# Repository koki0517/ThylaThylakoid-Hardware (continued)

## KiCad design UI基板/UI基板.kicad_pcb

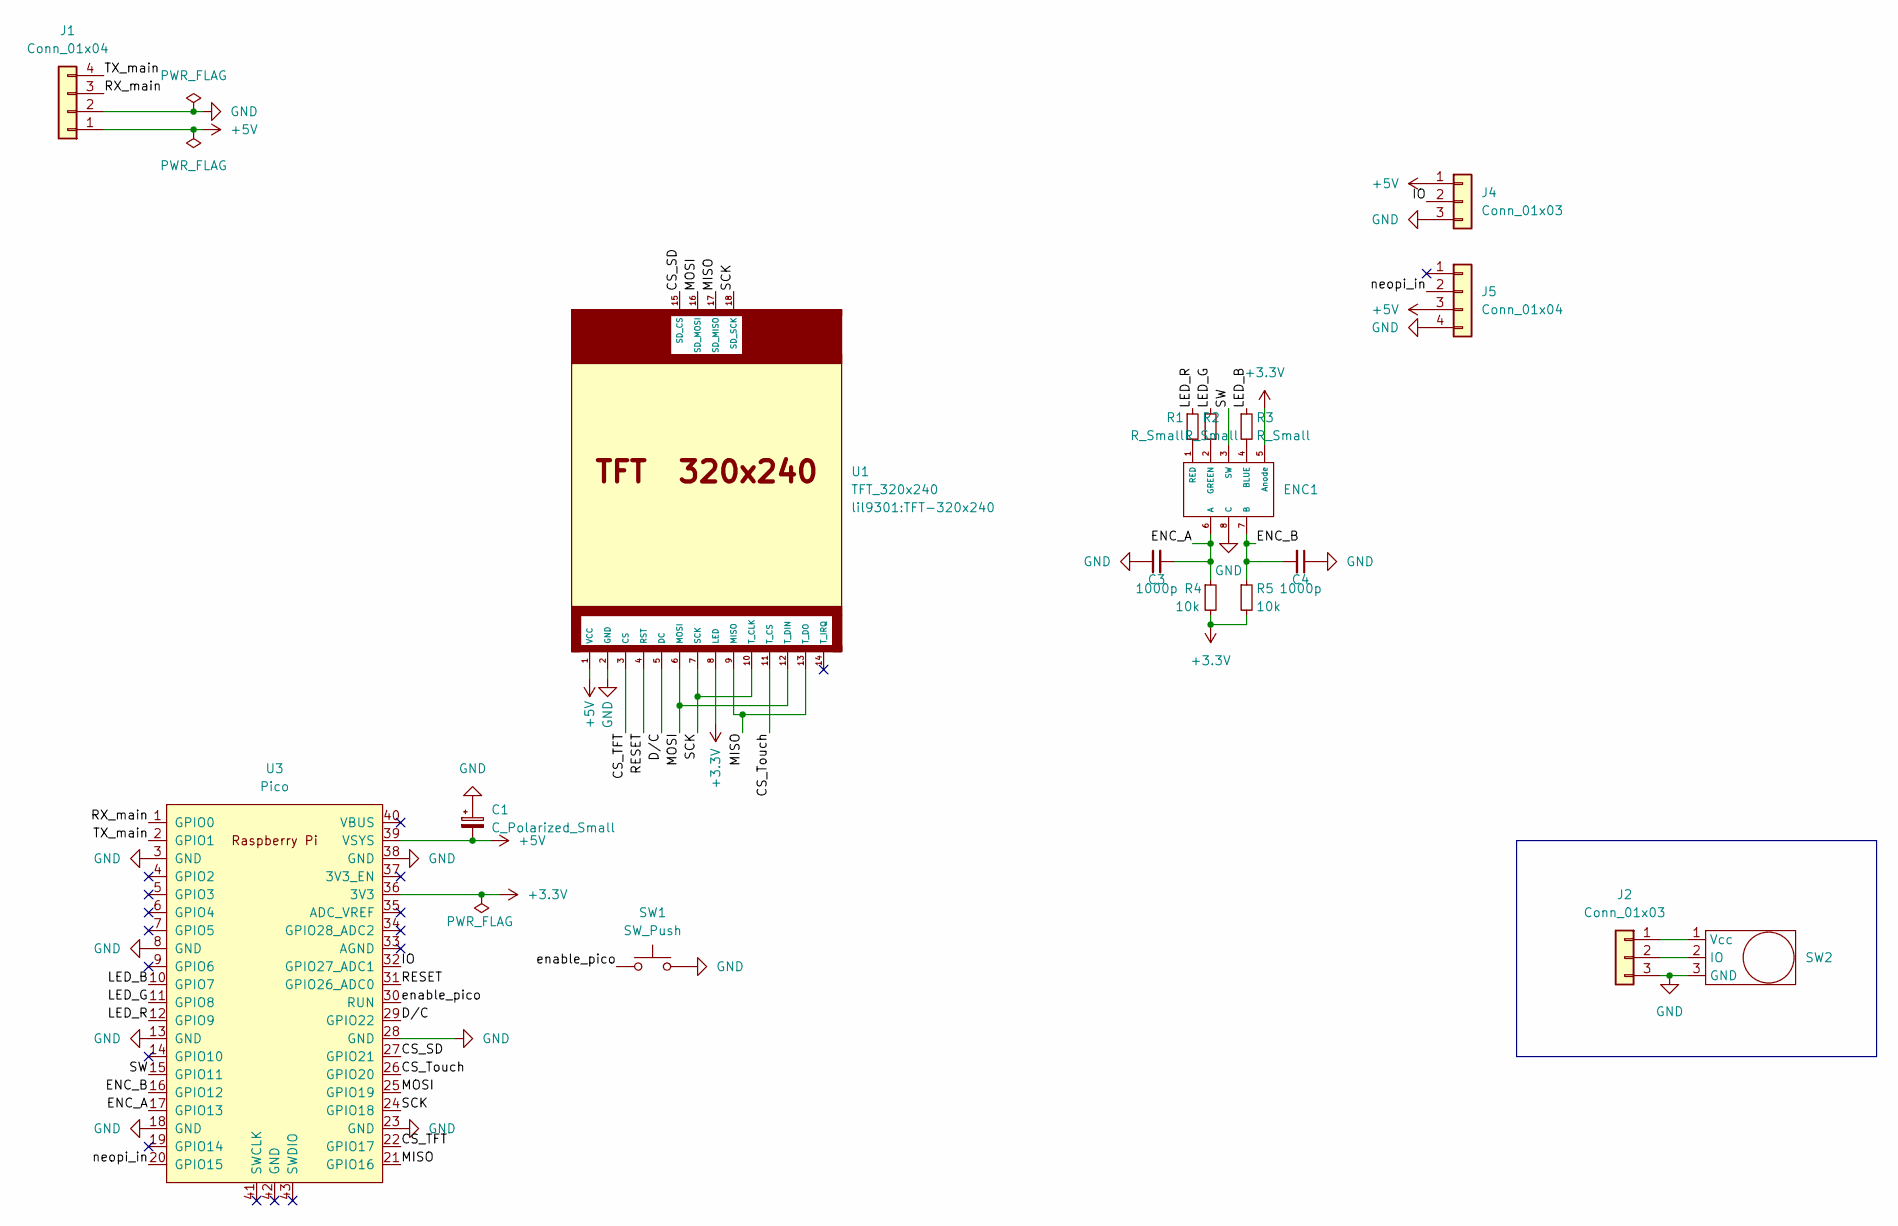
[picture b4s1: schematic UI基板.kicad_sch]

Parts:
C1: C_Polarized_Small; CP_Radial_D5.0mm_P2.50mm
C3, C4: 1000p; C_0603_1608Metric_Pad1.08x0.95mm_HandSolder
ENC1: EC12PLRGBSDVBF_DIP
J1: Conn_01x04; JST_XH_S4B-XH-A_1x04_P2.50mm_Horizontal
J2, J4: Conn_01x03; JST_XH_S3B-XH-A_1x03_P2.50mm_Horizontal
J5: Conn_01x04; GROVE-HW4-2.0-90D
R1, R2, R3: R_Small; R_0603_1608Metric_Pad0.98x0.95mm_HandSolder
R4, R5: 10k; R_0603_1608Metric_Pad0.98x0.95mm_HandSolder
SW1: SW_Push; SW_PUSH_6mm_H4.3mm
SW2: TTP223
U1: TFT_320x240; TFT-320x240
U3: Pico; RPi_Pico_SMD_TH

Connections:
+3.3V: ENC1.5 (Anode), R4.2, R5.2, U1.8 (LED), U3.36 (3V3)
+5V: C1.2, J1.1, J4.1, J5.3, U1.1 (VCC), U3.39 (VSYS)
/CS_SD: U1.15 (SD_CS), U3.27 (GPIO21)
/CS_TFT: U1.3 (CS), U3.22 (GPIO17)
/CS_Touch: U1.11 (T_CS), U3.26 (GPIO20)
/D/C: U1.5 (DC), U3.29 (GPIO22)
/ENC_A: C3.2, ENC1.6 (A), R4.1, U3.17 (GPIO13)
/ENC_B: C4.2, ENC1.7 (B), R5.1, U3.16 (GPIO12)
/IO: J4.2, U3.32 (GPIO27_ADC1)
/LED_B: R3.1, U3.10 (GPIO7)
/LED_G: R2.1, U3.11 (GPIO8)
/LED_R: R1.1, U3.12 (GPIO9)
/MISO: U1.9 (MISO), U1.13 (T_DO), U1.17 (SD_MISO), U3.21 (GPIO16)
/MOSI: U1.6 (MOSI), U1.12 (T_DIN), U1.16 (SD_MOSI), U3.25 (GPIO19)
/RESET: U1.4 (RST), U3.31 (GPIO26_ADC0)
/RX_main: J1.3, U3.1 (GPIO0)
/SCK: U1.7 (SCK), U1.10 (T_CLK), U1.18 (SD_SCK), U3.24 (GPIO18)
/SW: ENC1.3 (SW), U3.15 (GPIO11)
/TX_main: J1.4, U3.2 (GPIO1)
/enable_pico: SW1.1, U3.30 (RUN)
/neopi_in: J5.2, U3.20 (GPIO15)
GND: C1.1, C3.1, C4.1, ENC1.8 (C), J1.2, J2.3, J4.3, J5.4, SW1.2, SW2.3 (GND), U1.2 (GND), U3.3 (GND), U3.8 (GND), U3.13 (GND), U3.18 (GND), U3.23 (GND), U3.28 (GND), U3.38 (GND)
unnamed: ENC1.4 (BLUE), R3.2
unnamed: ENC1.2 (GREEN), R2.2
unnamed: ENC1.1 (RED), R1.2
unnamed: J2.1, SW2.1 (Vcc)
unnamed: J2.2, SW2.2 (IO)

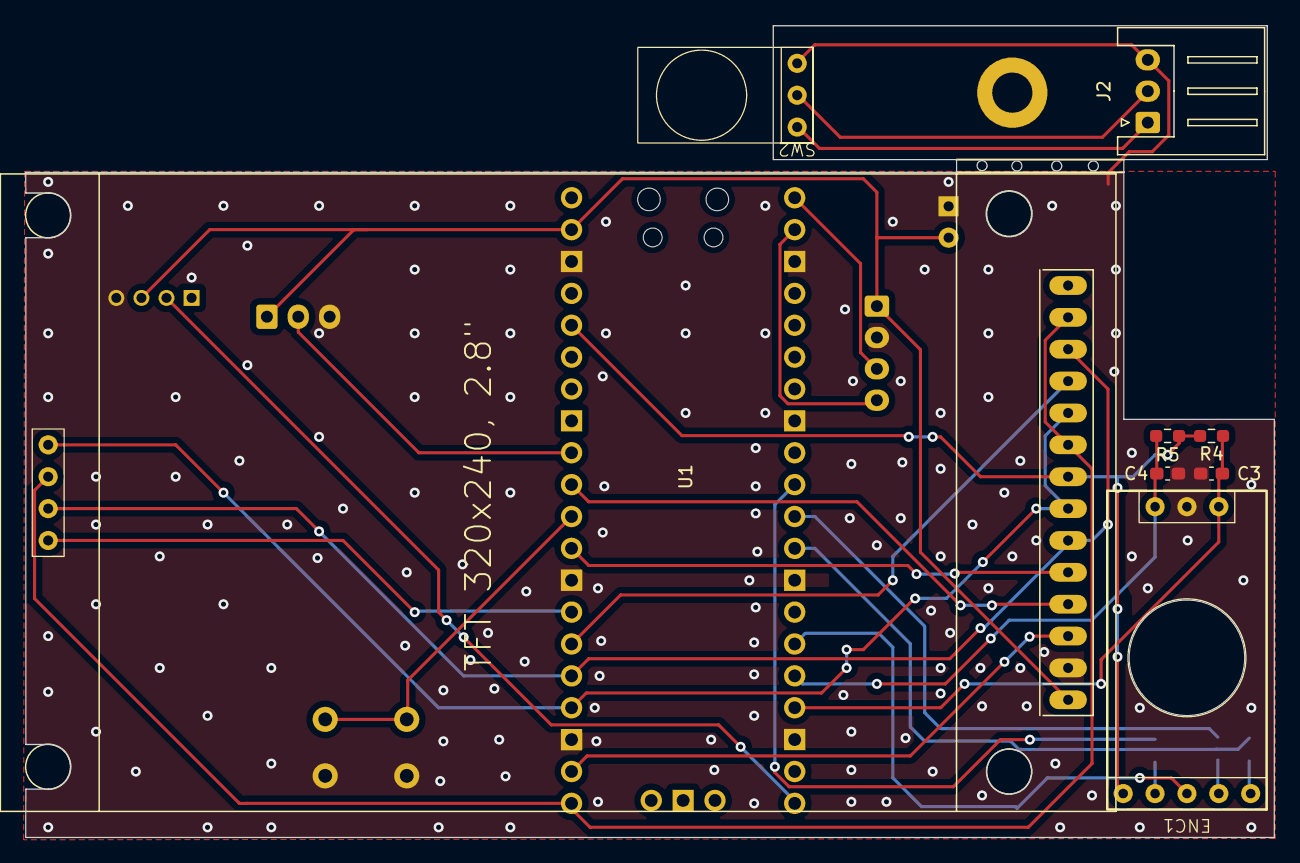
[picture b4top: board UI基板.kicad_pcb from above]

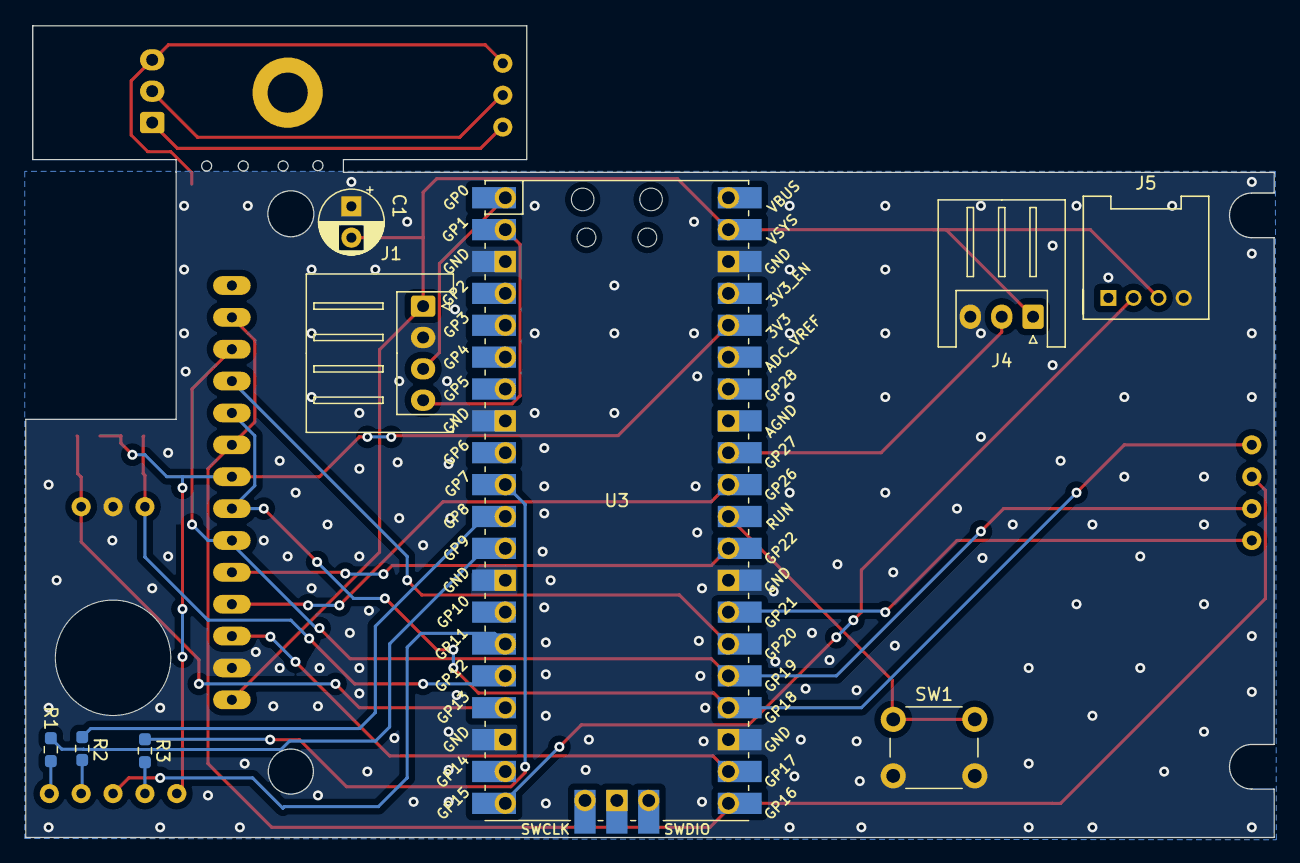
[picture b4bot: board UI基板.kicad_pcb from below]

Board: 2 copper layers, 99.5 x 64.7 mm, 17 parts (9 on the bottom side), 27 nets.

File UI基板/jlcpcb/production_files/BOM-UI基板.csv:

Comment,Designator,Footprint,LCSC
TFT_320x240,U1,TFT-320x240,
~,ENC1,EC12PLRGBSDVBF_DIP,
C_Polarized_Small,C1,CP_Radial_D5.0mm_P2.50mm,
Pico,U3,RPi_Pico_SMD_TH,
SW_Push,SW1,SW_PUSH_6mm_H4.3mm,
Conn_01x03,J4,JST_XH_S3B-XH-A_1x03_P2.50mm_Horizontal,
R_Small,R1,R_0603_1608Metric_Pad0.98x0.95mm_HandSolder,
R_Small,R2,R_0603_1608Metric_Pad0.98x0.95mm_HandSolder,
R_Small,R3,R_0603_1608Metric_Pad0.98x0.95mm_HandSolder,
1000p,C4,C_0603_1608Metric_Pad1.08x0.95mm_HandSolder,
1000p,C3,C_0603_1608Metric_Pad1.08x0.95mm_HandSolder,
Conn_01x04,J1,JST_XH_S4B-XH-A_1x04_P2.50mm_Horizontal,
10k,R4,R_0603_1608Metric_Pad0.98x0.95mm_HandSolder,
10k,R5,R_0603_1608Metric_Pad0.98x0.95mm_HandSolder,
Conn_01x04,J5,GROVE-HW4-2.0-90D,
~,SW2,TTP223,
Conn_01x03,J2,JST_XH_S3B-XH-A_1x03_P2.50mm_Horizontal,

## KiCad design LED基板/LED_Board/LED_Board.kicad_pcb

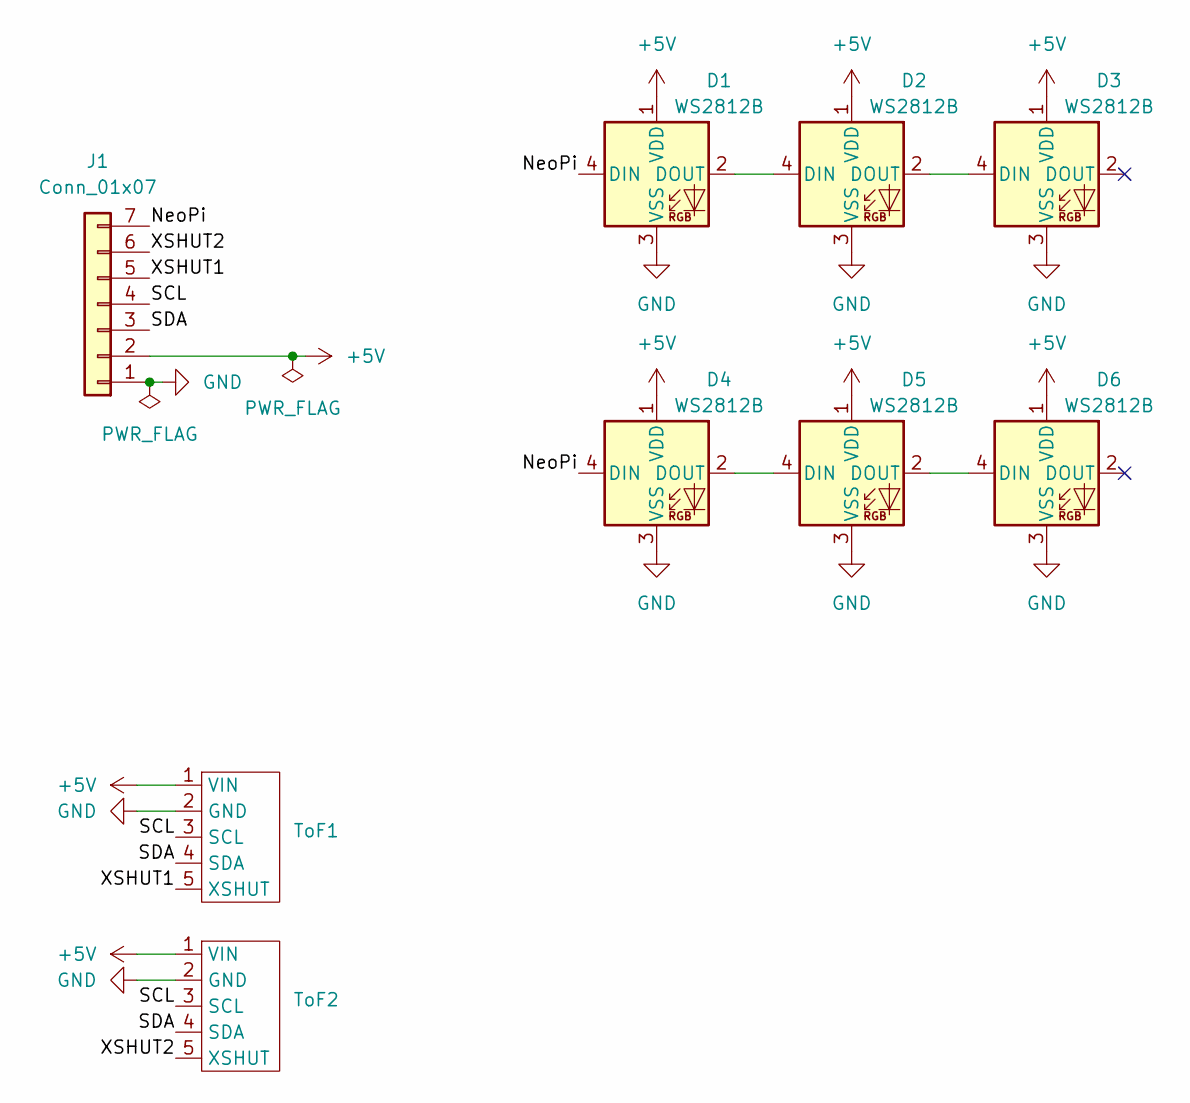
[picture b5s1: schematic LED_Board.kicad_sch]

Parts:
D1, D2, D3, D4, D5, D6: WS2812B; LED_WS2812B_PLCC4_5.0x5.0mm_P3.2mm
J1: Conn_01x07; PinHeader_1x07_P2.54mm_Horizontal
ToF1, ToF2: GY530

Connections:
+5V: D1.1 (VDD), D2.1 (VDD), D3.1 (VDD), D4.1 (VDD), D5.1 (VDD), D6.1 (VDD), J1.2, ToF1.1 (VIN), ToF2.1 (VIN)
/NeoPi: D1.4 (DIN), D4.4 (DIN), J1.7
/SCL: J1.4, ToF1.3 (SCL), ToF2.3 (SCL)
/SDA: J1.3, ToF1.4 (SDA), ToF2.4 (SDA)
/XSHUT1: J1.5, ToF1.5 (XSHUT)
/XSHUT2: J1.6, ToF2.5 (XSHUT)
GND: D1.3 (VSS), D2.3 (VSS), D3.3 (VSS), D4.3 (VSS), D5.3 (VSS), D6.3 (VSS), J1.1, ToF1.2 (GND), ToF2.2 (GND)
unnamed: D1.2 (DOUT), D2.4 (DIN)
unnamed: D2.2 (DOUT), D3.4 (DIN)
unnamed: D4.2 (DOUT), D5.4 (DIN)
unnamed: D5.2 (DOUT), D6.4 (DIN)

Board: 2 copper layers, 9 parts (0 on the bottom side), 11 nets, no tracks yet.

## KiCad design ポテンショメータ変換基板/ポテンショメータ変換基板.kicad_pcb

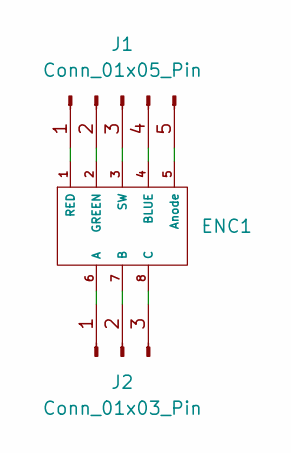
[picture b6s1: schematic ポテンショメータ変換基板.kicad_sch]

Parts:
ENC1: EC12PLRGBSDVBF
J1: Conn_01x05_Pin; PinHeader_1x05_P2.54mm_Vertical
J2: Conn_01x03_Pin; PinHeader_1x03_P2.54mm_Vertical

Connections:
unnamed: ENC1.6 (A), J2.1
unnamed: ENC1.5 (Anode), J1.5
unnamed: ENC1.7 (B), J2.2
unnamed: ENC1.4 (BLUE), J1.4
unnamed: ENC1.8 (C), J2.3
unnamed: ENC1.2 (GREEN), J1.2
unnamed: ENC1.1 (RED), J1.1
unnamed: ENC1.3 (SW), J1.3

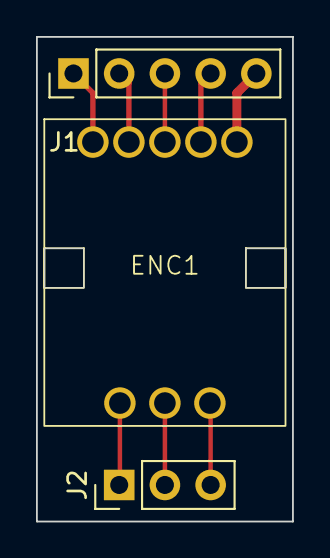
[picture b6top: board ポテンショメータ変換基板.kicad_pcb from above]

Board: 2 copper layers, 14.2 x 26.9 mm, 3 parts (0 on the bottom side), 8 nets.

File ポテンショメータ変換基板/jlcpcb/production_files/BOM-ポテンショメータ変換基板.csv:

Comment,Designator,Footprint,LCSC
Conn_01x03_Pin,J2,PinHeader_1x03_P2.54mm_Vertical,
Conn_01x05_Pin,J1,PinHeader_1x05_P2.54mm_Vertical,
~,ENC1,EC12PLRGBSDVBF,

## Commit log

2024-09-16 電源基板とハンドルバー
2024-09-17 フルカラーLEDロータリーエンコーダDIP変換基板
2024-09-18 パスコンと保護ダイオードの追加
2024-09-20 ほげほげ
2024-09-23 メイン基板の概形を追加
2024-09-26 サーボ基板
2024-10-06 メイン基板
2024-10-15 UI基板
2024-10-19 電源基板
    白色にして発注
2024-10-26 main
2024-11-05 電源基板にATtiny用LDOを追加
